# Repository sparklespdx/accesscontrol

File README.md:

accesscontrol
=============

Access Control System Software

This is the software for the access control system created for [Ctrl-H](http://ctrlh.org/),
a hackerspace in Portland, OR.  

ARCHIVE NOTES BELOW THIS POINT
------------------------------
Schematics will be available at some point.  Check out the [Instructable](http://www.instructables.com/id/RFID-Access-Control-System/).

Uses the Raspberry Pi GPIO module from https://pypi.python.org/pypi/RPi.GPIO/ .

contact rmiller @ duskglow dot com with questions.

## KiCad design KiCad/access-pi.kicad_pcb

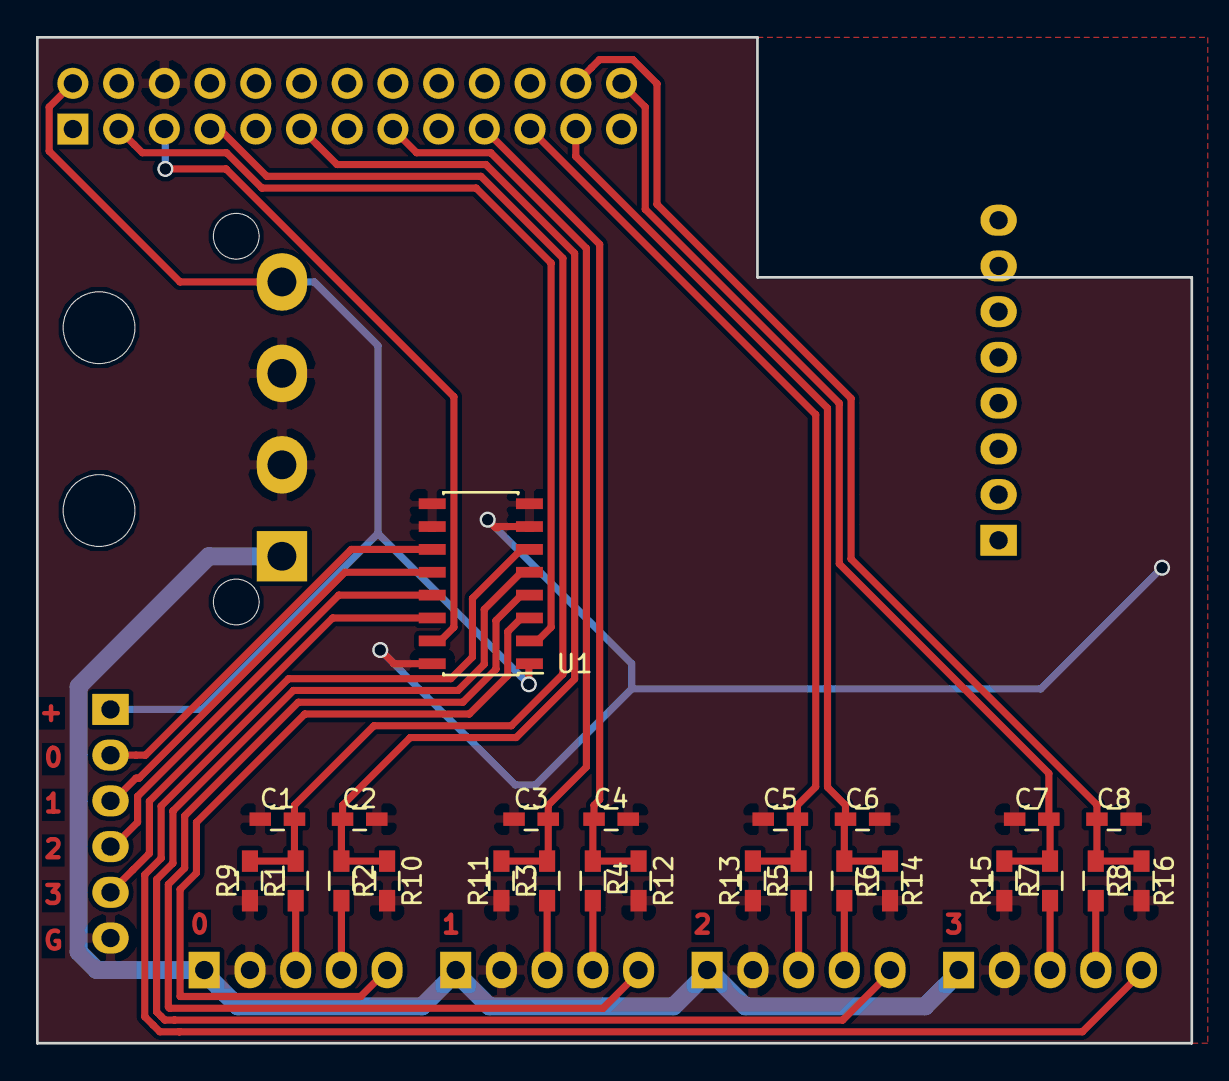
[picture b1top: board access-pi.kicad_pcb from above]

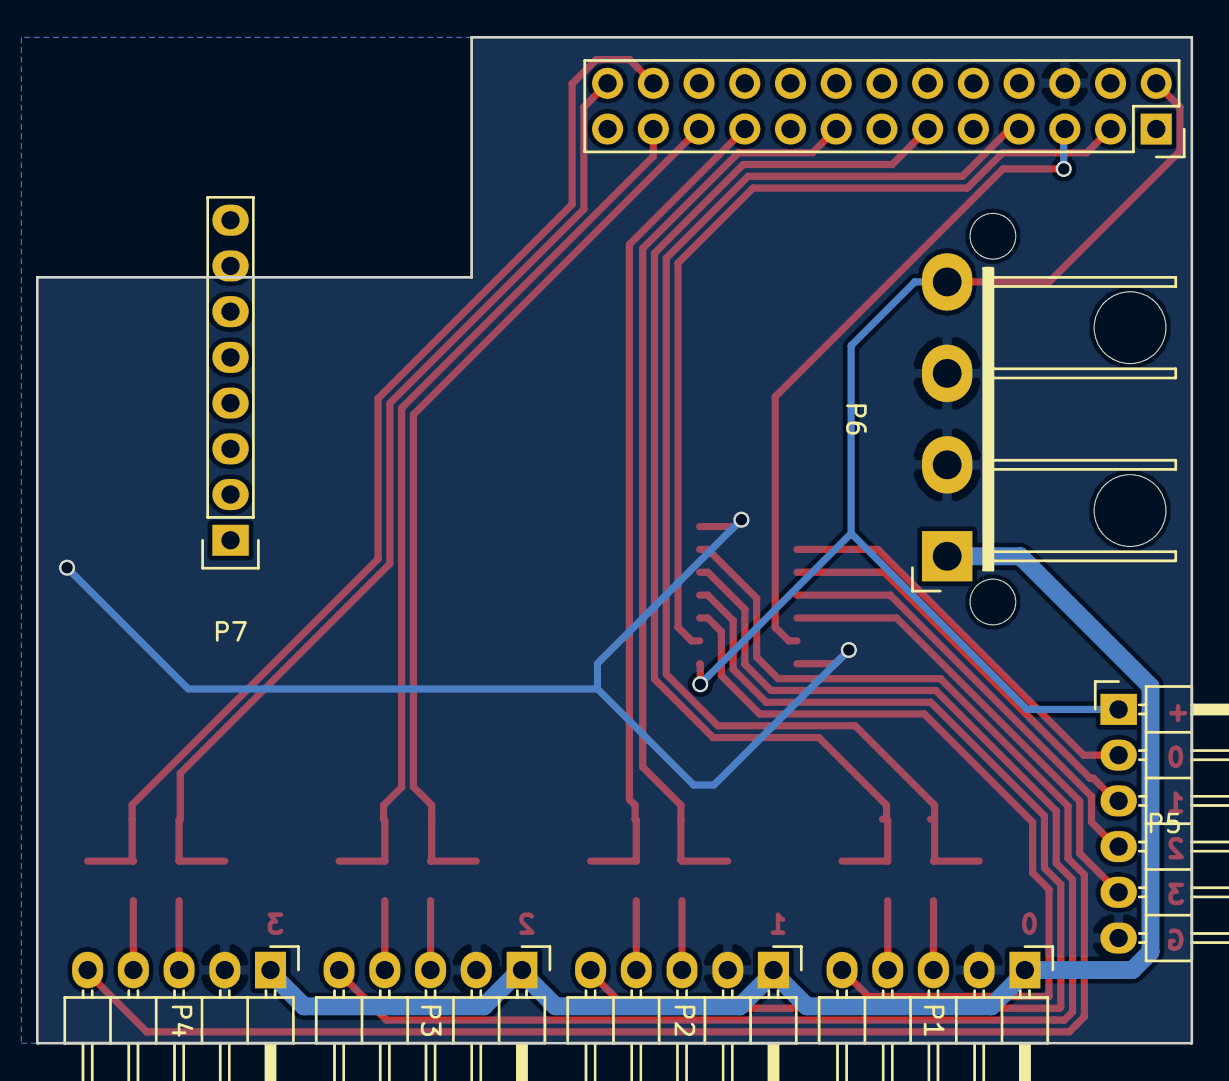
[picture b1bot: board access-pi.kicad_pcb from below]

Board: 2 copper layers, 64.1 x 55.9 mm, 33 parts (8 on the bottom side), 29 nets.

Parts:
C1, C2, C3, C4, C5, C6, C7, C8: 1n; C_0603_HandSoldering
P1, P2, P3, P4: CONN_01X05; Pin_Header_Angled_1x05
P5: CONN_01X06; Pin_Header_Angled_1x06
P6: Molex_8981; Molex_15-24-4441
P7: CONN_01X08; Pin_Header_Straight_1x08
R1, R2, R3, R4, R5, R6, R7, R8: 12k7; R_0603_HandSoldering
R9, R10, R11, R12, R13, R14, R15, R16: 22k; R_0603_HandSoldering
RPi1: RASPBERRY_IO; Socket_Strip_Straight_2x13
U1: TPIC2810; SOIC-16_3.9x9.9mm_Pitch1.27mm

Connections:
+5V: P5.1, P6.4, RPi1.2, U1.1
+12V: P1.1, P2.1, P3.1, P4.1, P6.1
/R0_D0: P1.3, R1.2
/R0_D1: P1.4, R2.2
/R0_LED: P1.5, U1.3
/R1_D0: P2.3, R3.2
/R1_D1: P2.4, R4.2
/R1_LED: P2.5, U1.4
/R2_D0: P3.3, R5.2
/R2_D1: P3.4, R6.2
/R2_LED: P3.5, U1.5
/R3_D0: P4.3, R7.2
/R3_D1: P4.4, R8.2
/R3_LED: P4.5, U1.6
GND: C1.1, C2.1, C3.1, C4.1, C5.1, C6.1, C7.1, C8.1, P1.2, P2.2, P3.2, P4.2, P5.6, P6.2, P6.3, R9.1, R10.1, R11.1, R12.1, R13.1, R14.1, R15.1, R16.1, RPi1.6, U1.7, U1.8, U1.9, U1.10, U1.16
unnamed: C1.2, R1.1, R9.2, RPi1.7
unnamed: C2.2, R2.1, R10.2, RPi1.11
unnamed: C3.2, R3.1, R11.2, RPi1.15
unnamed: C4.2, R4.1, R12.2, RPi1.19
unnamed: C5.2, R5.1, R13.2, RPi1.21
unnamed: C6.2, R6.1, R14.2, RPi1.23
unnamed: C7.2, R7.1, R15.2, RPi1.26
unnamed: C8.2, R8.1, R16.2, RPi1.24
unnamed: P5.2, U1.11
unnamed: P5.3, U1.12
unnamed: P5.4, U1.13
unnamed: P5.5, U1.14
unnamed: RPi1.3, U1.2
unnamed: RPi1.5, U1.15

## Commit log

2015-02-16 Flushing old Arduino Yun code.
2015-02-16 Freshening for the latest Raspberry Pi goodness
2015-02-16 Create log file for any debug output
2015-02-17 ignore things from ide
2015-02-17 imports and whitespace
2015-02-17 requirements
2015-02-17 started redesigning configs simplified objects instead of globals
2015-05-08 Add vim temp files to gitignore
2015-05-08 Try not to crash when rehashing with bad user file
2015-05-12 More work on objects, tested good but sloppy
    This is working with the 4-door reader hardware but it needs
    serious cleanup and review.
2015-05-12 How to push back to origin? Try this...
2015-05-13 Misc cleanup and working lockers
2015-05-14 Fixed confusing local use of global object name
2015-05-14 Minor cleanup and formatting
2016-02-08 Startup from crontab a little faster with @reboot
2016-02-08 Latest RPi.GPIO and simplify install paths
2016-02-08 Add hostname to reports for multi-host facilities
2016-02-08 Flush prints so debug.log isn't blocked
2016-02-08 Background python so we don't block cron
2017-02-12 Added notes for installing from fresh raspbian
2017-02-12 Added board design files for old Raspberry Pi
2017-02-12 All documents get old. Especially this one. Halp!
2019-06-05 Refactor for event mode master key
    Looks like I replaced some tabs with spaces too
2019-06-06 Match our test bed
2019-06-06 Refactor lock/unlock to its own function
2019-06-06 Tweaked implementation of event mode
    Refactored to support new mode: in order to unlock a door, an authorized
    user must open the door, and then scan the "event mode" key within 10
    seconds. The door is re-locked by swiping the "event mode" key.
2019-06-06 Make event mode timeout configurable
2019-06-06 Configure if event mode even works
    Unless "event_mode_timeout" is configured on a reader, event mode will
    not work.
2019-06-06 fix example config
2019-06-06 Remove pyc file
2019-08-05 fixed toggle_lock() logger message typo
2019-08-05 Let people with "event mode" unlock doors directly
2019-08-05 Change "event mode" permission to "event host"
2019-08-05 Allow debug_mode to be set in the config file
2019-08-05 Make the abbreviation of last-names configurable
2019-08-05 Make output to green LED configurable
2019-08-05 Fix classless call typo
2019-08-05 Make the i2c bus number configurable
2019-08-05 Demoted "Initializing" message from report to debug
2019-08-05 Preserve conf directory during git pull
2019-08-05 Use example configs if conf dir doesn't exist
2019-09-06 Added webapp and frontend
2019-09-06 Need to return readers so we can use them in the webapp
